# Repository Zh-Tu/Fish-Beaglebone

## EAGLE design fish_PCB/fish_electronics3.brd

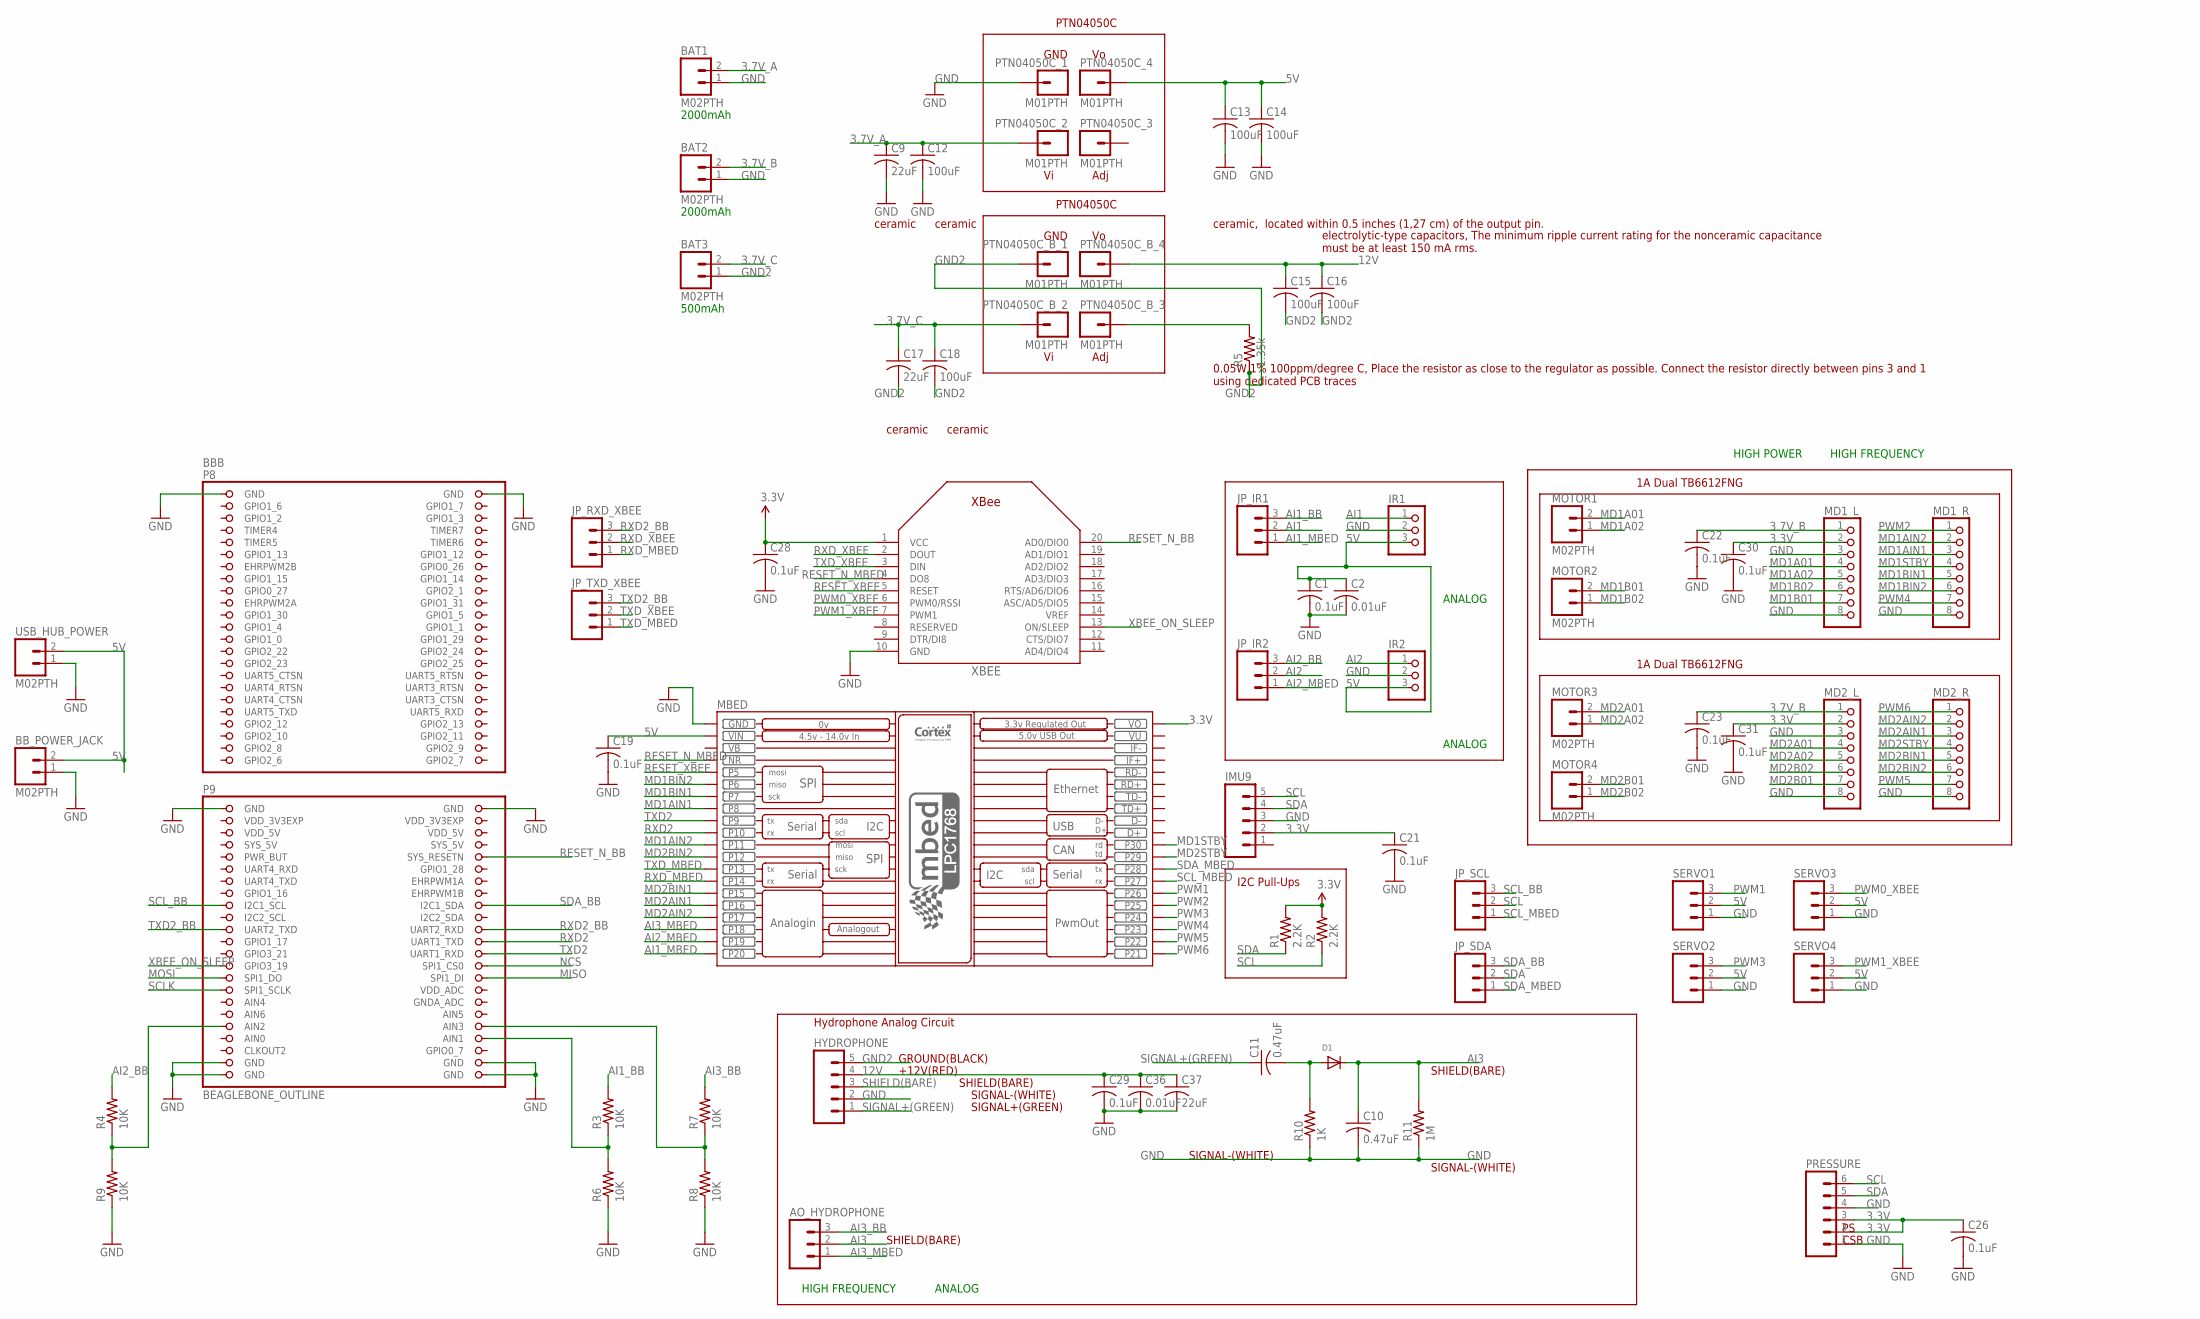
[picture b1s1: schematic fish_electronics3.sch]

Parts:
AO_HYDROPHONE: M03PTH; 1X03
BAT1, BAT2, BAT3: M02PTH; 1X02
BBB: BEAGLEBONE_OUTLINE; BEAGLEBONE_SHIELD
BB_POWER_JACK: M02PTH; 1X02
C1, C19, C21, C22, C23, C26, C28, C29, C30, C31: 0.1uF; C0805
C2, C36: 0.01uF; C0805
C9, C17, C37: 22uF; C0805
C10, C11: 0.47uF; C0805
C12, C13, C14, C18: 100uF; C1206
C15, C16: 100uF; C1210
D1: DIODESOT23_WAVE; SOT23-W
HYDROPHONE: M05PTH; 1X05
IMU9: M05PTH; 1X05
IR1, IR2: PINHD-1X3CB; 1X03-CLEANBIG
JP_IR1, JP_IR2: M03PTH; 1X03
JP_RXD_XBEE: M03PTH; 1X03
JP_SCL: M03PTH; 1X03
JP_SDA: M03PTH; 1X03
JP_TXD_XBEE: M03PTH; 1X03
MBED: MBED_NXP_LPC1768; MBED-KIT
MD1_L, MD1_R, MD2_L, MD2_R: PINHD-1X8; 1X08
MOTOR1, MOTOR2, MOTOR3, MOTOR4: M02PTH; 1X02
PRESSURE: M06SIP; 1X06
PTN04050C_1, PTN04050C_2, PTN04050C_3, PTN04050C_4, PTN04050C_B_1, PTN04050C_B_2, PTN04050C_B_3, PTN04050C_B_4: M01PTH; 1X01
R1, R2: 2.2K; R0805
R3, R4, R6, R7, R8, R9: 10K; R0805
R5: 1.35k; R0805
R10: 1K; R0805
R11: 1M; R0805
SERVO1, SERVO2, SERVO3, SERVO4: M03PTH; 1X03
USB_HUB_POWER: M02PTH; 1X02
XBEE: XBEE

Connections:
3.3V: C21.1, C26.1, C28.1, C30.1, C31.1, IMU9.2, MBED.VOUT (VO), MD1_L.2, MD2_L.2, PRESSURE.2, PRESSURE.3, R1.2, R2.2, XBEE.1 (VCC)
3.7V_A: BAT1.2, C9.1, C12.1, PTN04050C_2.1
3.7V_B: BAT2.2, C22.1, C23.1, MD1_L.1, MD2_L.1
3.7V_C: BAT3.2, C17.1, C18.1, PTN04050C_B_2.1
5V: BB_POWER_JACK.2, C1.1, C2.1, C13.1, C14.1, C19.1, IR1.3, IR2.3, MBED.VIN, PTN04050C_4.1, SERVO1.2, SERVO2.2, SERVO3.2, SERVO4.2, USB_HUB_POWER.2
12V: C15.1, C16.1, C29.1, C36.1, C37.1, HYDROPHONE.4, PTN04050C_B_4.1
AI1: IR1.1, JP_IR1.2
AI1_BB: JP_IR1.3, R3.2
AI1_MBED: JP_IR1.1, MBED.P$20 (P20)
AI2: IR2.1, JP_IR2.2
AI2_BB: JP_IR2.3, R4.2
AI2_MBED: JP_IR2.1, MBED.P$19 (P19)
AI3: AO_HYDROPHONE.2, C10.1, D1.3 (C), R11.2
AI3_BB: AO_HYDROPHONE.3, R7.2
AI3_MBED: AO_HYDROPHONE.1, MBED.P$18 (P18)
AIN0: BBB.85 (AIN0)
GND: BAT1.1, BAT2.1, BBB.1 (GND), BBB.2 (GND), BBB.47 (GND), BBB.48 (GND), BBB.89 (GND), BBB.90 (GND), BBB.91 (GND), BBB.92 (GND), BB_POWER_JACK.1, C1.2, C2.2, C9.2, C10.2, C12.2, C13.2, C14.2, C19.2, C21.2, C22.2, C23.2, C26.2, C28.2, C29.2, C30.2, C31.2, C36.2, C37.2, HYDROPHONE.2, IMU9.3, IR1.2, IR2.2, MBED.GND, MD1_L.3, MD1_L.8, MD1_R.8, MD2_L.3, MD2_L.8, MD2_R.8, PRESSURE.1, PRESSURE.4, PTN04050C_1.1, R6.1, R8.1, R9.1, R10.1, R11.1, SERVO1.1, SERVO2.1, SERVO3.1, SERVO4.1, USB_HUB_POWER.1, XBEE.10 (GND)
GND2: BAT3.1, C15.2, C16.2, C17.2, C18.2, HYDROPHONE.5, PTN04050C_B_1.1, R5.1
MD1A01: MD1_L.4, MOTOR1.2
MD1A02: MD1_L.5, MOTOR1.1
MD1AIN1: MBED.P$8 (P8), MD1_R.3
MD1AIN2: MBED.P$11 (P11), MD1_R.2
MD1B01: MD1_L.7, MOTOR2.2
MD1B02: MD1_L.6, MOTOR2.1
MD1BIN1: MBED.P$7 (P7), MD1_R.5
MD1BIN2: MBED.P$6 (P6), MD1_R.6
MD1STBY: MBED.P$30 (P30), MD1_R.4
MD2A01: MD2_L.4, MOTOR3.2
MD2A02: MD2_L.5, MOTOR3.1
MD2AIN1: MBED.P$16 (P16), MD2_R.3
MD2AIN2: MBED.P$17 (P17), MD2_R.2
MD2B01: MD2_L.7, MOTOR4.2
MD2B02: MD2_L.6, MOTOR4.1
MD2BIN1: MBED.P$15 (P15), MD2_R.5
MD2BIN2: MBED.P$12 (P12), MD2_R.6
MD2STBY: MBED.P$29 (P29), MD2_R.4
MISO: BBB.76 (SPI1_DI)
MOSI: BBB.75 (SPI1_DO)
unnamed: BBB.86 (AIN1), R3.1, R6.2
unnamed: PTN04050C_B_3.1, R5.2
unnamed: BBB.84 (AIN3), R7.1, R8.2
unnamed: BBB.83 (AIN2), R4.1, R9.2
unnamed: C11.2, D1.1 (A), R10.2
NCS: BBB.74 (SPI1_CS0)
PWM0_XBEE: SERVO3.3, XBEE.6 (PWM0/RSSI)
PWM1: MBED.P$26 (P26), SERVO1.3
PWM1_XBEE: SERVO4.3, XBEE.7 (PWM1)
PWM2: MBED.P$25 (P25), MD1_R.1
PWM3: MBED.P$24 (P24), SERVO2.3
PWM4: MBED.P$23 (P23), MD1_R.7
PWM5: MBED.P$22 (P22), MD2_R.7
PWM6: MBED.P$21 (P21), MD2_R.1
RESET_N_BB: BBB.56 (SYS_RESETN), XBEE.20 (AD0/DIO0)
RESET_N_MBED: MBED.NR, XBEE.4 (DO8)
RESET_XBEE: MBED.P$5 (P5), XBEE.5 (RESET)
RXD2: BBB.70 (UART1_TXD), MBED.P$10 (P10)
RXD2_BB: BBB.68 (UART2_RXD), JP_RXD_XBEE.3
RXD_MBED: JP_RXD_XBEE.1, MBED.P$14 (P14)
RXD_XBEE: JP_RXD_XBEE.2, XBEE.2 (DOUT)
SCL: IMU9.5, JP_SCL.2, PRESSURE.6, R2.1
SCLK: BBB.77 (SPI1_SCLK)
SCL_BB: BBB.63 (I2C1_SCL), JP_SCL.3
SCL_MBED: JP_SCL.1, MBED.P$27 (P27)
SDA: IMU9.4, JP_SDA.2, PRESSURE.5, R1.1
SDA_BB: BBB.64 (I2C1_SDA), JP_SDA.3
SDA_MBED: JP_SDA.1, MBED.P$28 (P28)
SHIELD(BARE): HYDROPHONE.3
SIGNAL+(GREEN): C11.1, HYDROPHONE.1
SYS_5V: BBB.53 (SYS_5V)
TXD2: BBB.72 (UART1_RXD), MBED.P$9 (P9)
TXD2_BB: BBB.67 (UART2_TXD), JP_TXD_XBEE.3
TXD_MBED: JP_TXD_XBEE.1, MBED.P$13 (P13)
TXD_XBEE: JP_TXD_XBEE.2, XBEE.3 (DIN)
VB: MBED.VB
VDD_3V3EXP: BBB.49 (VDD_3V3EXP), BBB.50 (VDD_3V3EXP)
VDD_5V: BBB.51 (VDD_5V), BBB.52 (VDD_5V)
VU: MBED.VU
XBEE_ON_SLEEP: BBB.73 (GPIO3_19), XBEE.13 (ON/SLEEP)

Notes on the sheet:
I2C Pull-Ups
GND
Adj
PTN04050C
0.05W 1% 100ppm/degree C, Place the resistor as close to the regulator as possible. Connect the resistor directly between pins 3 and 1 using dedicated PCB traces
ceramic
electrolytic-type capacitors, The minimum ripple current rating for the nonceramic capacitance must be at least 150 mA rms.
ceramic, located within 0.5 inches (1,27 cm) of the output pin.
Hydrophone Analog Circuit
1A Dual TB6612FNG
GROUND(BLACK)
+12V(RED)
SHIELD(BARE)
SIGNAL-(WHITE)
SIGNAL+(GREEN)
CSB
HIGH POWER
HIGH FREQUENCY
ANALOG
2000mAh
500mAh

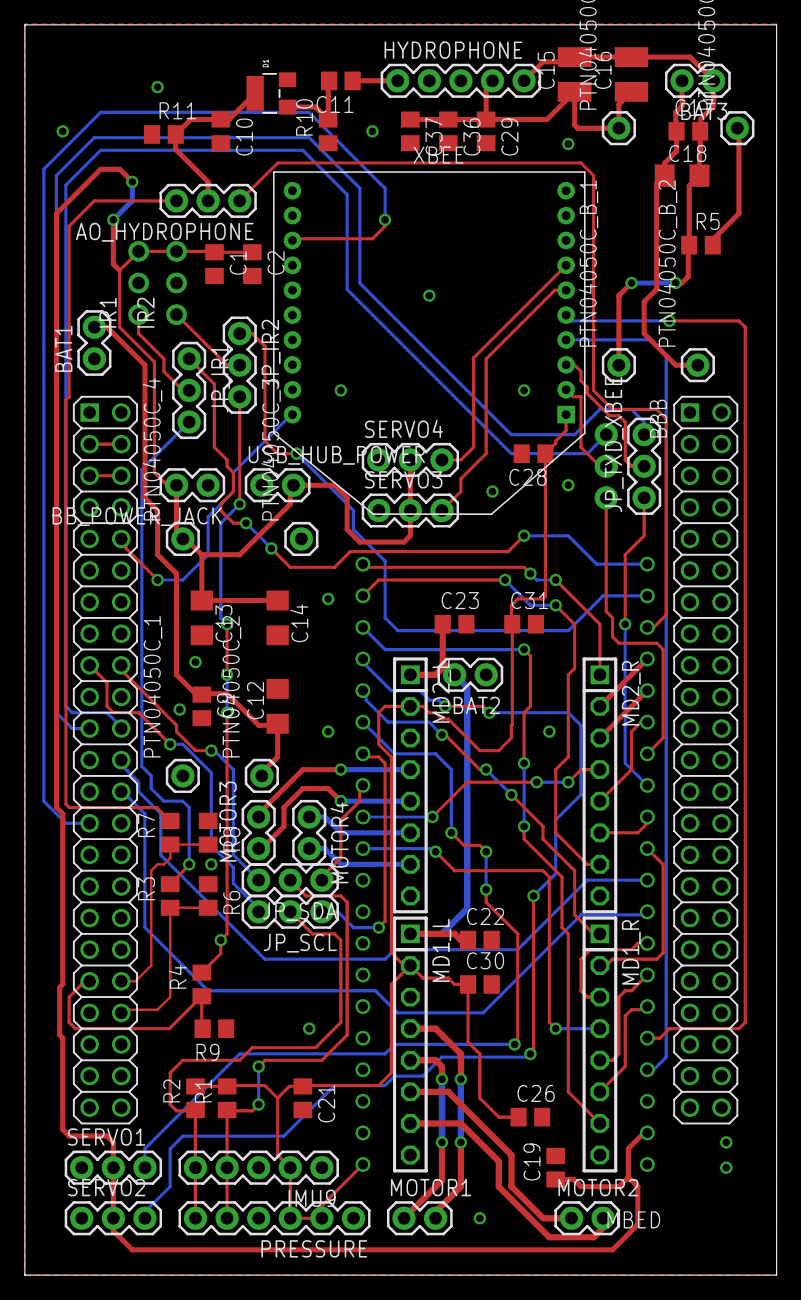
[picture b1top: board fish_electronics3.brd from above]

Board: 2 copper layers, 60.4 x 100.5 mm, 75 parts (1 on the bottom side), 69 nets.

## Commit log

2015-08-30 :confetti_ball: Added .gitattributes & .gitignore files
2015-08-30 Fish robot Beaglebone+Mbed

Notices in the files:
parts and their libraries:
SparkFun: Licensing: CC v3.0 Share-Alike You are welcome to use this library for commercial purposes.
